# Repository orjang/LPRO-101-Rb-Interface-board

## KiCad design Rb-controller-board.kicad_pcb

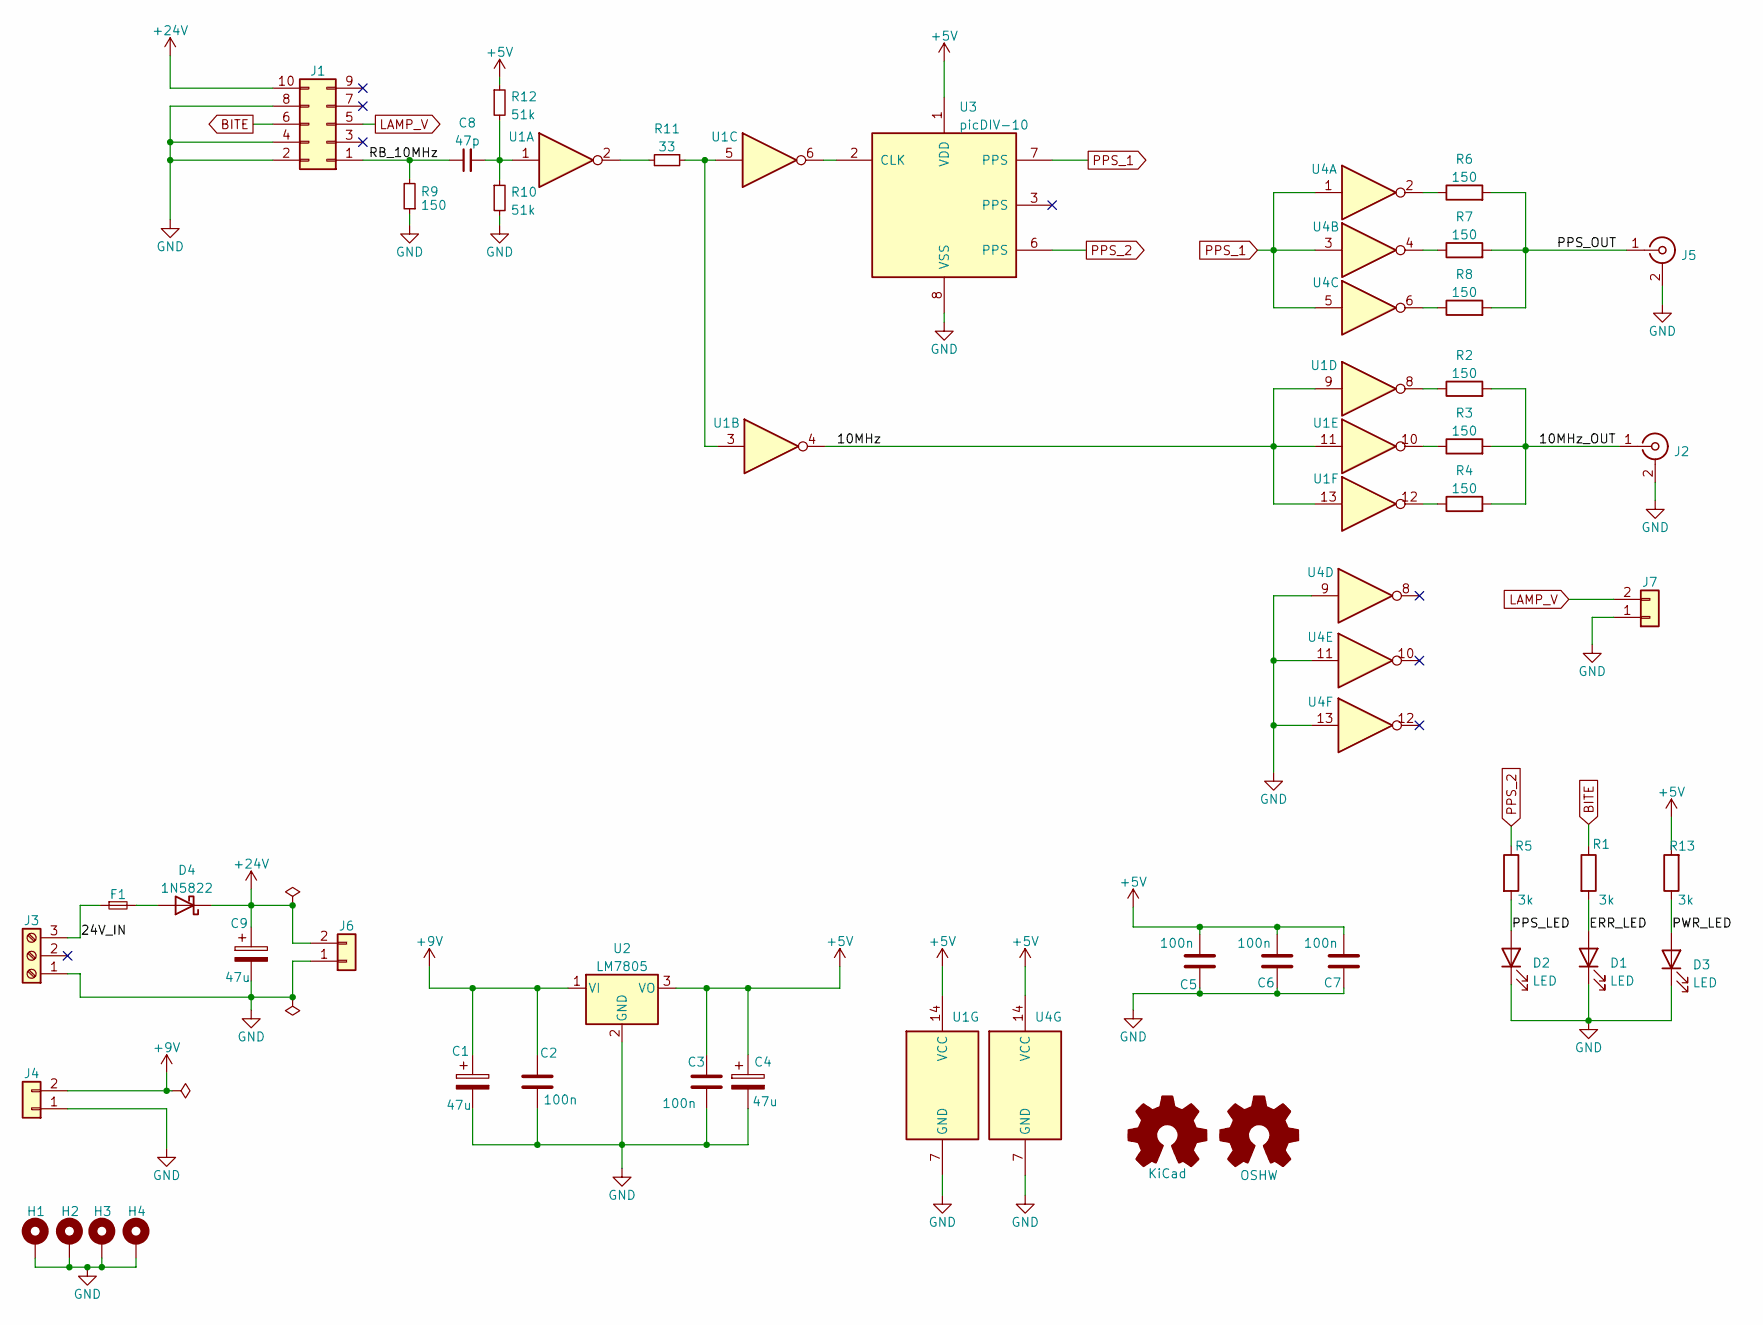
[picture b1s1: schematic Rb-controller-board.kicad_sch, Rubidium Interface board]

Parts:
C1, C4, C9: 47u; CP_Radial_D6.3mm_P2.50mm
C2, C3, C5, C6, C7: 100n; C_1206_3216Metric
C8: 47p; C_1206_3216Metric
D1, D2, D3: LED; LED_D4.0mm
D4: 1N5822; D_DO-201AD_P12.70mm_Horizontal
F1: Fuse_Small; Fuseholder_Cylinder-5x20mm_Stelvio_Kontek_Horizontal_Open
H1, H2, H3, H4: MountingHole_Pad; MountingHole_2.7mm_M2.5_Pad
J1: Conn_02x05_Odd_Even; PinHeader_2x05_P2.54mm_Vertical
J2, J5: Conn_Coaxial; BNC_Linx_CONBNC002_Horizontal
J3: Screw_Terminal_01x03; TerminalBlock_bornier-3_P5.08mm
J4, J6, J7: Conn_01x02; PinHeader_1x02_P2.54mm_Vertical
LOGO1: KiCad; KiCad-Logo2_5mm_SilkScreen
LOGO2: OSHW; OSHW-Logo2_7.3x6mm_SilkScreen
R1, R5, R13: 3k; R_1206_3216Metric
R2, R3, R4, R6, R7, R8, R9: 150; R_1206_3216Metric
R10, R12: 51k; R_1206_3216Metric
R11: 33; R_1206_3216Metric
U1, U4: 74AC04; DIP-14_W7.62mm
U2: LM7805; TO-220-3_Horizontal_TabDown
U3: picDIV-10; DIP-8_W7.62mm

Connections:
+5V: C3.1, C4.1, C5.2, C6.2, C7.2, R12.1, R13.2, U1.14 (VCC), U2.3 (VO), U3.1 (VDD), U4.14 (VCC)
+9V: C1.1, C2.1, J4.2, U2.1 (VI)
+24V: C9.1, D4.1 (K), J1.10, J6.2
/10MHz: U1.4, U1.9, U1.11, U1.13
/10MHz_OUT: J2.1 (In), R2.2, R3.2, R4.2
/24V_IN: F1.1, J3.3
/ERR_LED: D1.2 (A), R1.2
/PPS_LED: D2.2 (A), R5.2
/PPS_OUT: J5.1 (In), R6.2, R7.2, R8.2
/PWR_LED: D3.2 (A), R13.1
/RB_10MHz: C8.1, J1.1, R9.2
BITE: J1.6, R1.1
GND: C1.2, C2.2, C3.2, C4.2, C5.1, C6.1, C7.1, C9.2, D1.1 (K), D2.1 (K), D3.1 (K), H1.1, H2.1, H3.1, H4.1, J1.2, J1.4, J1.8, J2.2 (Ext), J3.1, J4.1, J5.2 (Ext), J6.1, J7.1, R9.1, R10.2, U1.7 (GND), U2.2 (GND), U3.8 (VSS), U4.7 (GND), U4.9, U4.11, U4.13
LAMP_V: J1.5, J7.2
unnamed: C8.2, R10.1, R12.2, U1.1
unnamed: D4.2 (A), F1.2
unnamed: R2.1, U1.8
unnamed: R3.1, U1.10
unnamed: R4.1, U1.12
unnamed: R6.1, U4.2
unnamed: R7.1, U4.4
unnamed: R8.1, U4.6
unnamed: R11.1, U1.3, U1.5
unnamed: R11.2, U1.2
unnamed: U1.6, U3.2 (CLK)
PPS_1: U3.7 (PPS), U4.1, U4.3, U4.5
PPS_2: R5.1, U3.6 (PPS)

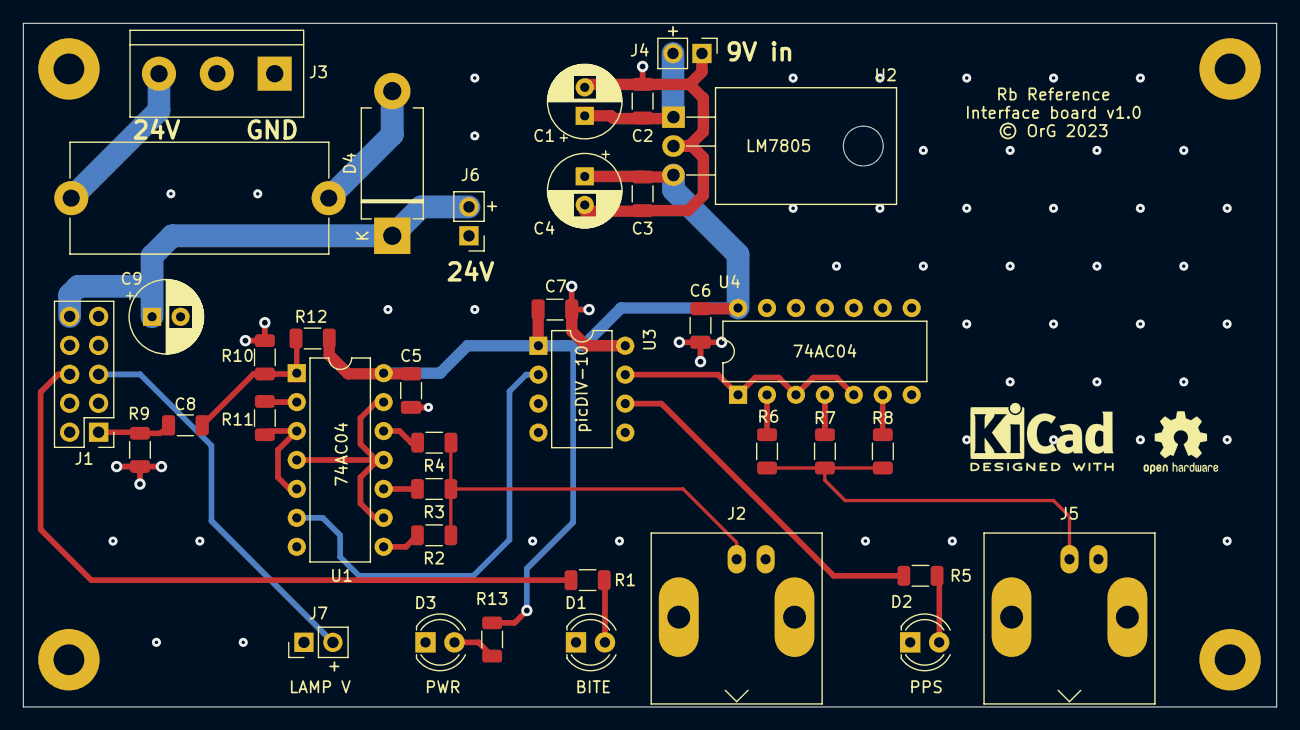
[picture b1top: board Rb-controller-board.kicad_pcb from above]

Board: 4 copper layers, 110.0 x 60.0 mm, 44 parts (0 on the bottom side), 27 nets.

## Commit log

2023-01-03 First version of Rb interface board
2023-03-10 Adjusted resistor values
    RF termination resistor changed to 150 ohm to better match ribbon cable impedance.
    Lower LED series resitors to 3k

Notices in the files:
Rb-controller-board.kicad_pcb:
© OrG 2023
